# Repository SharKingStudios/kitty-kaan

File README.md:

# kitty kaan

*Acceleration controlled cat ears for our FRC driver ;)*

## What is this?

**kitty kaan** is a wearable pair of motorized cat ears designed for our FRC driver. The ears react to acceleration, making them move with the driver in a more expressive way.

The project combines a small electronics stack and compact mounting hardware into a lightweight assembly. An accelerometer detects motion, and the control electronics translate that movement into ear movement. The result is a simple but very silly accessory that gives the driver a pair of responsive “kitty ears.”

This was designed as a small CAD and electronics integration project. A big part of the challenge was packaging everything into the smallest form factor possible while still keeping the assembly buildable. Instead of using one large controller board, the electronics were split across smaller breakout boards so they could fit into tighter spaces and be arranged more flexibly.

---

## Renders

---

## Some context

Its a simpler project for a simple idea.

The goal was to make the electronics stack as small as physically possible, which is why seperate breakouts were used. They also added to the simplicity of the design (which is nice).

Fitting everything together was the hardest part of this mini project, but it turned out looking pretty awesome!

## Journaling

This project was made for Hack Club's Stasis program!

You can check out my project journal [here](https://stasis.hackclub.com/dashboard/projects/cmni7bl1i00i401np7ca4izak)!

## Bill of Materials

| Qty | Item | URL | Unit Price (USD) | Total (USD) | Notes |
| ---: | --- | --- | ---: | ---: | --- |
| 1 | Adafruit MiniBoost 5V @ 1A - TPS61023 | [adafruit.com/product/4654](https://www.adafruit.com/product/4654) | $3.95 | $3.95 |  |
| 1 | 9g Servo Set | [Amazon](https://www.amazon.com/Control-Raspberry-Helicopter-Airplane-Controls/dp/B0DFL7QZRJ) | $6.99 | $6.99 | For 4× 9g servos |
| 1 | Seeed XIAO RA4M1 | [Amazon](https://www.amazon.com/Compatible-Arduino-Renesas-Tolerant-Ultra-Compact/dp/B0DF9VJDJ7) | $9.90 | $9.90 |  |
| 1 | JST Battery Connector | — | $0.00 | $0.00 | Whatever matches your battery |
| 1 | Some Battery | — | $0.00 | $0.00 | Pick your favorite |
| 1 | MPU-6050 IMU | [Amazon](https://www.amazon.com/HiLetgo-MPU-6050-Accelerometer-Gyroscope-Converter/dp/B01DK83ZYQ) | $6.99 | $6.99 |  |
| 1 | PCB + Shipping | JLCPCB | $15.00 | $15.00 |  |
|  | **Total** |  |  | **$42.83** |  |

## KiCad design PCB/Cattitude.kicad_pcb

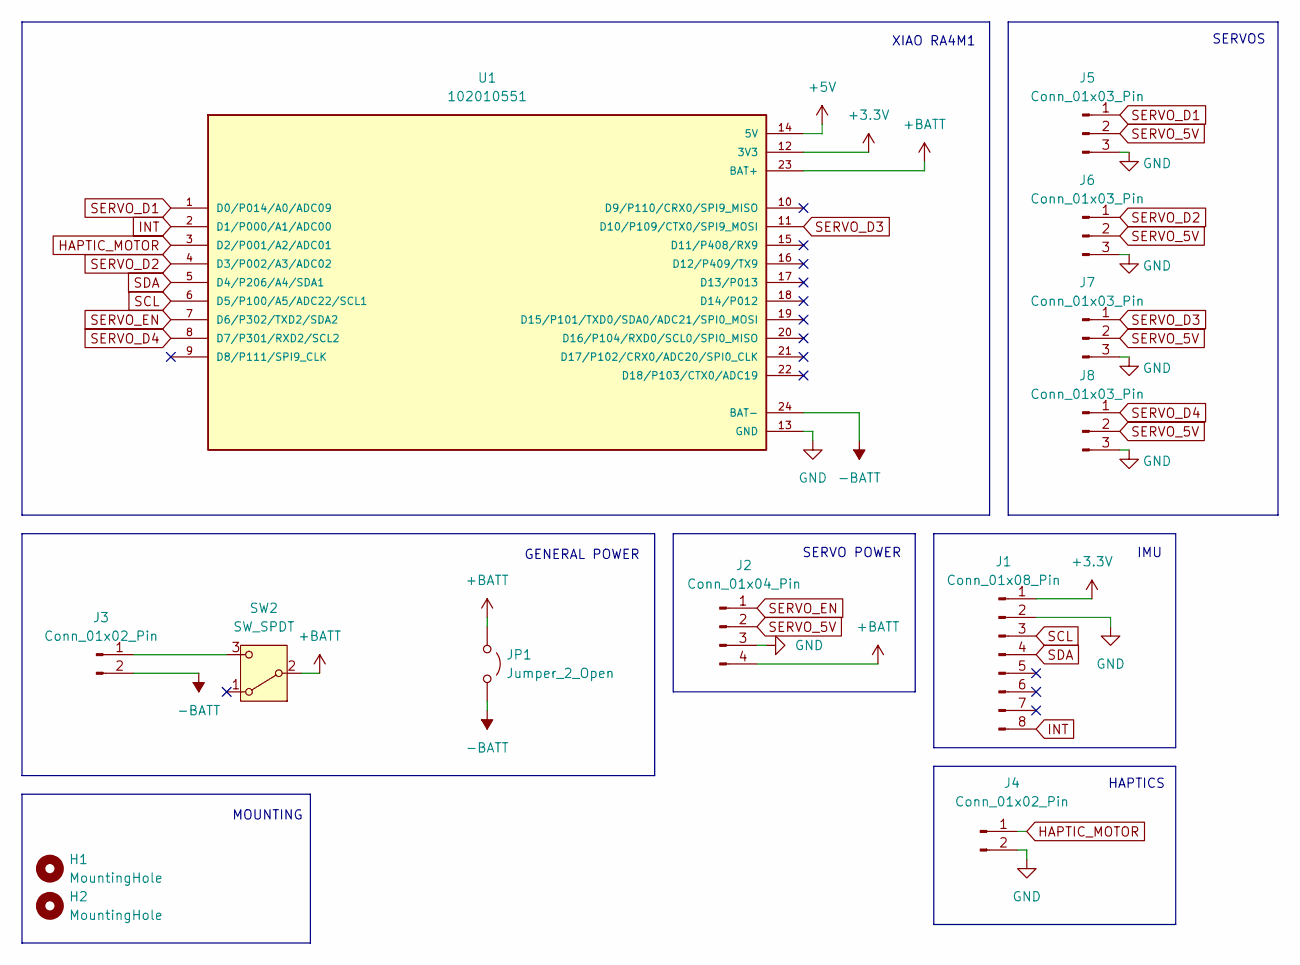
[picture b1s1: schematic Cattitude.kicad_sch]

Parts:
H1, H2: MountingHole; MountingHole_2.7mm_M2.5_DIN965_Pad
J1: Conn_01x08_Pin; MPU 6050
J2: Conn_01x04_Pin; PinHeader_1x04_P2.54mm_Vertical
J3: Conn_01x02_Pin; JST_EH_B2B-EH-A_1x02_P2.50mm_Vertical
J4: Conn_01x02_Pin; PinHeader_1x02_P2.54mm_Vertical
J5, J6, J7, J8: Conn_01x03_Pin; PinHeader_1x03_P2.54mm_Horizontal
JP1: Jumper_2_Open; TestPoint_2Pads_Pitch2.54mm_Drill0.8mm
SW2: SW_SPDT; SW_Slide_SPDT_Angled_CK_OS102011MA1Q
U1: 102010551; XIAO RA4M1; PARTREV NA

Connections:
+3.3V: J1.1, U1.12 (3V3)
+5V: U1.14 (5V)
+BATT: J2.4, JP1.1 (A), SW2.2 (B), U1.23 (BAT+)
-BATT: J3.2, JP1.2 (B), U1.24 (BAT-)
GND: J1.2, J2.3, J4.2, J5.3, J6.3, J7.3, J8.3, U1.13 (GND)
HAPTIC_MOTOR: J4.1, U1.3 (D2/P001/A2/ADC01)
INT: J1.8, U1.2 (D1/P000/A1/ADC00)
unnamed: J3.1, SW2.3 (C)
SCL: J1.3, U1.6 (D5/P100/A5/ADC22/SCL1)
SDA: J1.4, U1.5 (D4/P206/A4/SDA1)
SERVO_5V: J2.2, J5.2, J6.2, J7.2, J8.2
SERVO_D1: J5.1, U1.1 (D0/P014/A0/ADC09)
SERVO_D2: J6.1, U1.4 (D3/P002/A3/ADC02)
SERVO_D3: J7.1, U1.11 (D10/P109/CTX0/SPI9_MOSI)
SERVO_D4: J8.1, U1.8 (D7/P301/RXD2/SCL2)
SERVO_EN: J2.1, U1.7 (D6/P302/TXD2/SDA2)

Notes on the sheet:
SERVOS
MOUNTING
HAPTICS
XIAO RA4M1
SERVO POWER
GENERAL POWER
IMU

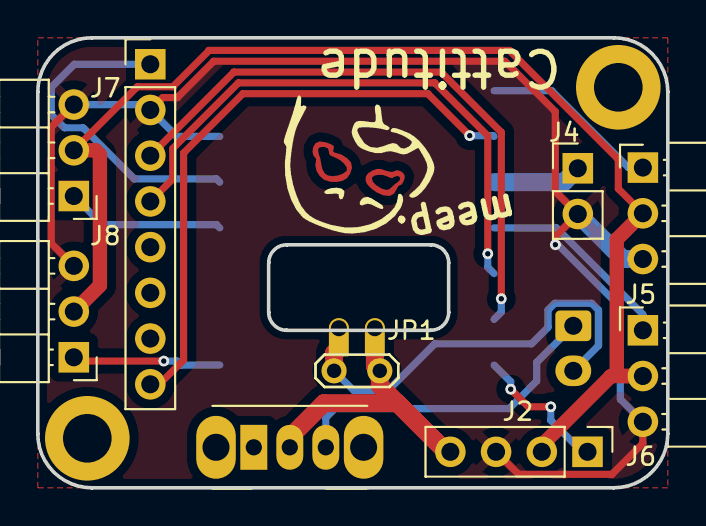
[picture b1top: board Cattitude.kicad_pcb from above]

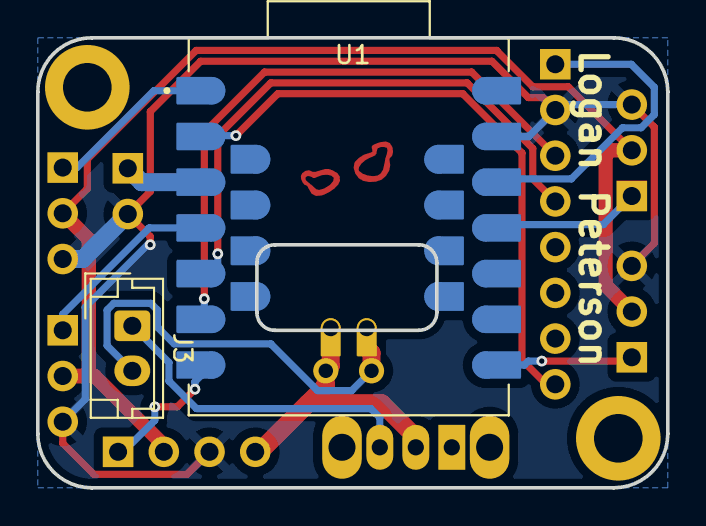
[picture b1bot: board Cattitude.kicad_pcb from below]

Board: 2 copper layers, 35.0 x 25.0 mm, 13 parts (2 on the bottom side), 15 nets.

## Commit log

2026-04-05 Imported Parts + Finished Schematic
2026-04-06 PCB Routing done
2026-04-06 Board Cleanup + Production Files
2026-04-06 Added GND Pour
2026-04-09 Add Bill of Materials (BOM) CSV file
2026-04-09 Add CAD Assembly
2026-04-09 Update README
    Added project context, renders, and journaling information to README.
2026-04-09 Revise BOM.csv with corrected prices and entries
    Updated prices and formatting for BOM items.
2026-05-03 Add initial firmware for Kitty Kaan Cat Ear
    Initial commit of firmware for Kitty Kaan Cat Ear project, including setup for IMU and servo control.
2026-05-09 Update README with project details and BOM
    Added project description and Bill of Materials to README.
